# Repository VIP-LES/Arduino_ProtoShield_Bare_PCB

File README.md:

Arduino RF Shield
=======================================

The Arduino RF Shield (based on the [SparkFun ProtoShield](https://www.sparkfun.com/products/11665)) connects a [RFM69 breakout board](https://www.sparkfun.com/products/12775), [logic level converter](https://www.sparkfun.com/products/12009), and LED to an Arduino Uno.

Repository Contents
-------------------
* **/Hardware** - All Eagle design files (.brd, .sch)

License Information
-------------------
The hardware is released under [Creative Commons ShareAlike 4.0 International](https://creativecommons.org/licenses/by-sa/4.0/). Modified from [SparkFun ProtoShield](https://github.com/sparkfun/Arduino_ProtoShield_Bare_PCB) to remove unused pads and add connections for RFM69.

Distributed as-is; no warranty is given.

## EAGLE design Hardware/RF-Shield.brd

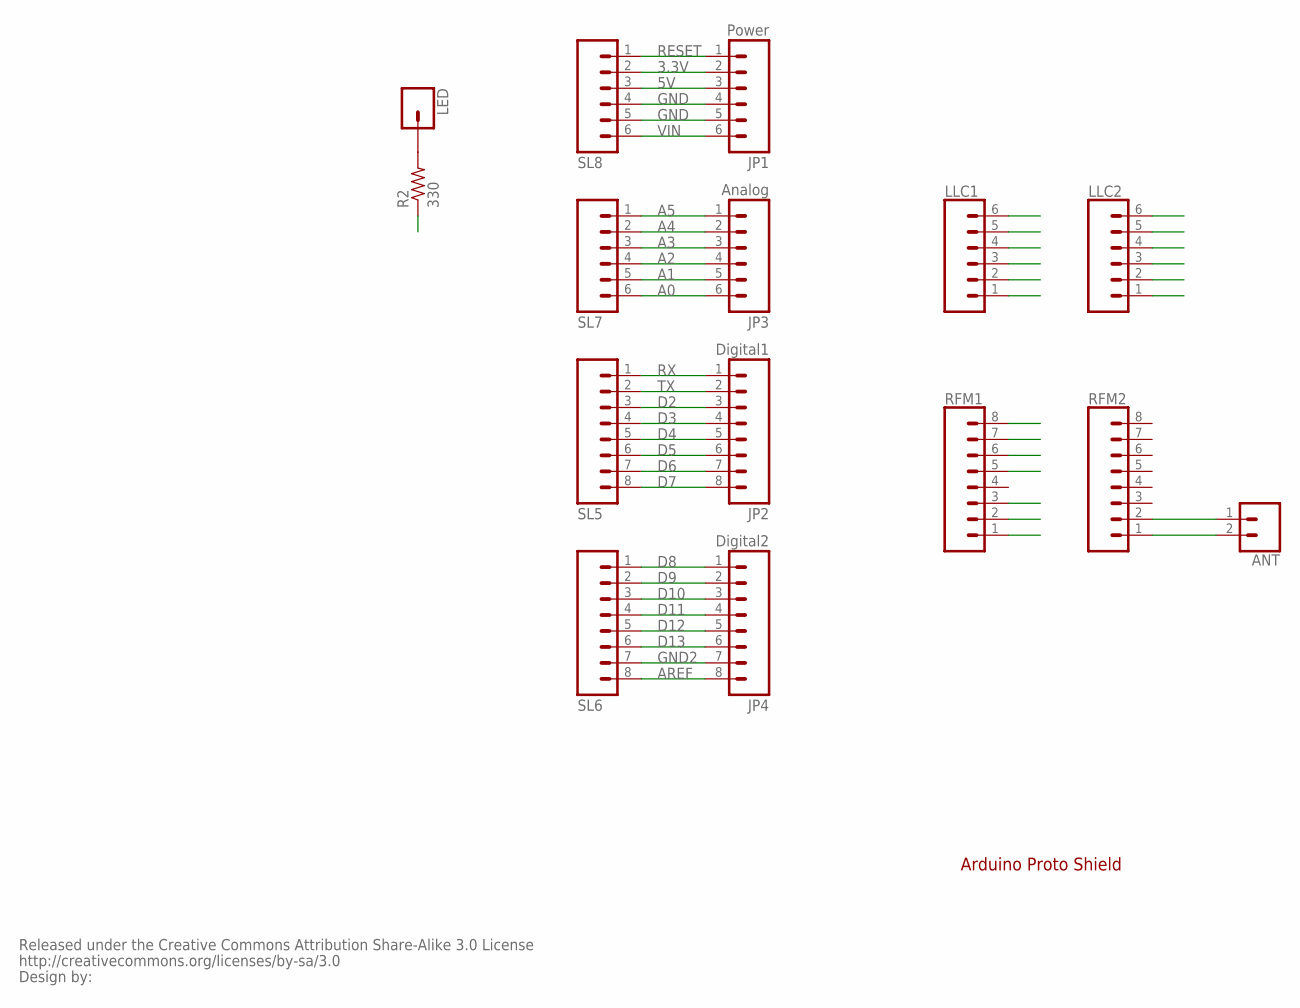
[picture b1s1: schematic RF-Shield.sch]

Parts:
ANT: CONN_021X02_NO_SILK; 1X02_NO_SILK
JP1: Power; 1X06
JP2: Digital1; 1X08
JP3: Analog; 1X06
JP4: Digital2; 1X08
LED: CONN_01PTH_NO_SILK_YES_STOP; 1X01_NO_SILK
LLC1, LLC2: CONN_06NO_SILK_NO_POP; 1X06_NO_SILK
R2: 330; AXIAL-0.3
RFM1, RFM2: CONN_08NO_SILK_FEMALE_PTH; 1X08_NO_SILK
SL5, SL6: M08; 1X08
SL7, SL8: M06SIP; 1X06
U$2: CREATIVE_COMMONS

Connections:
3.3V: JP1.2, LLC2.3, RFM1.1, SL8.2
5V: JP1.3, LLC1.3, SL8.3
A0: JP3.6, SL7.6
A1: JP3.5, SL7.5
A2: JP3.4, SL7.4
A3: JP3.3, SL7.3
A4: JP3.2, SL7.2
A5: JP3.1, SL7.1
ANT: ANT.1, RFM2.2
AREF: JP4.8, SL6.8
C: LLC2.2, RFM1.6
D2: JP2.3, RFM1.3, SL5.3
D3: JP2.4, SL5.4
D4: JP2.5, SL5.5
D5: JP2.6, SL5.6
D6: JP2.7, SL5.7
D7: JP2.8, SL5.8
D8: JP4.1, SL6.1
D9: JP4.2, SL6.2
D10: JP4.3, LLC1.1, SL6.3
D11: JP4.4, LLC1.5, SL6.4
D12: JP4.5, LLC1.6, SL6.5
D13: JP4.6, LLC1.2, SL6.6
GND: JP1.4, JP1.5, LLC1.4, LLC2.4, RFM1.2, SL8.4, SL8.5
GND2: JP4.7, R2.P$1 (1), SL6.7
GND3: ANT.2, RFM2.1
I: LLC2.5, RFM1.7
unnamed: LED.1, R2.P$2 (2)
O: LLC2.6, RFM1.8
RESET: JP1.1, SL8.1
RX: JP2.1, SL5.1
S: LLC2.1, RFM1.5
TX: JP2.2, SL5.2
VIN: JP1.6, SL8.6

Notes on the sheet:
Arduino Proto Shield

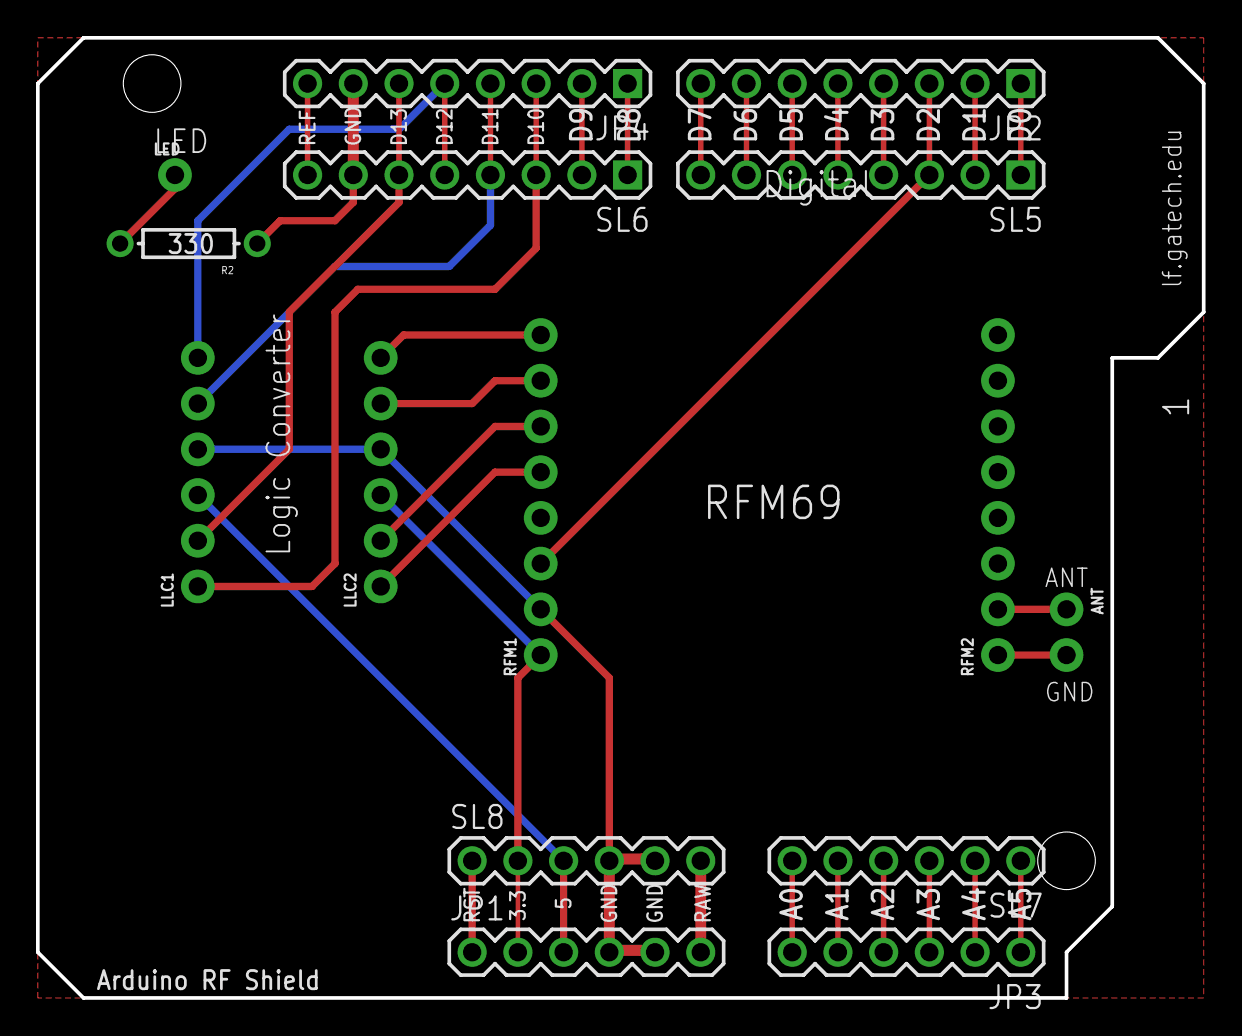
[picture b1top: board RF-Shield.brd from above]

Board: 2 copper layers, 64.8 x 53.3 mm, 16 parts (0 on the bottom side), 34 nets.

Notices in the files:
parts and their libraries:
SparkFun: Released under the Creative Commons Attribution Share-Alike 3.0 License
SparkFun: http://creativecommons.org/licenses/by-sa/3.0
SparkFun-Connectors: Licensing: Creative Commons ShareAlike 4.0 International - https://creativecommons.org/licenses/by-sa/4.0
